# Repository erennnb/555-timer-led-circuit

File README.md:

# ⚡ NE555 Timer — Blinking LED Circuit

\<p align="center">
&#x20; \<strong>A simple circuit. A fundamental concept. A step into electronics.\</strong>
\</p>

\<p align="center">
&#x20; Designed with ❤️ and \<strong>KiCad\</strong>
\</p>

---

## 🔎 About The Project

This project is a blinking LED circuit built around the **NE555 timer IC**, one of the most widely used integrated circuits in electronics.

The goal is to explore the fundamentals of timing circuits, understand how electronic components work together, and take the first steps toward PCB design.

What starts as a single blinking LED becomes an opportunity to learn circuit design, component selection, schematic capture, and PCB layout.

## 🎯 Project Goals

- Understand the fundamentals of the NE555 timer.
- Explore timing circuits and oscillation.
- Practice schematic design in KiCad.
- Learn component placement and PCB routing.
- Build a foundation for more advanced electronics projects.

## 🧩 Components

| Component      | Purpose                                          |
| -------------- | ------------------------------------------------ |
| NE555 timer IC | Generates timing pulses                          |
| Resistors      | Set timing characteristics and limit LED current |
| Capacitor(s)   | Determine timing behavior                        |
| LED            | Visual output indicator                          |
| Power supply   | Provides circuit power                           |

*Component values and the exact configuration are documented in the KiCad project files.*

## 🛠️ Tools & Technologies

\<p>
&#x20; \
&#x20; \
\</p>

- **EDA Software:** KiCad
- **Main IC:** NE555
- **Design:** Electronic schematic and PCB layout

## 📂 Project Structure

```text
555-timer-led-circuit/
├── README.md
├── 555-timer-led-circuit.kicad_pro
├── 555-timer-led-circuit.kicad_sch
└── 555-timer-led-circuit.kicad_pcb
```

*Filenames may differ depending on the actual project files.*

## ✅ Project Status

- [x] Schematic design
- [x] PCB layout
- [x] Design Rule Check (DRC)
- [ ] Hardware testing

## 🚀 What I Learned

- Translating a circuit idea into a schematic.
- Understanding the role of the NE555 timer.
- Organizing electronic components in a PCB design.
- Developing a structured electronics design workflow.

## 🔮 Future Improvements

- Calculate and measure the LED blinking frequency.
- Compare theoretical timing with measured results.
- Refine PCB component placement and routing.
- Explore additional NE555 operating modes.

## 👨‍💻 About Me

I am an Electrical and Electronics Engineering student building practical skills in electronics, PCB design, and embedded systems.

This project is part of my journey from learning circuit fundamentals to designing more advanced electronic systems.

**One circuit at a time. One concept at a time.**

---

\<p align="center">
&#x20; \<i>Learning by designing, improving by building.\</i>
\</p>

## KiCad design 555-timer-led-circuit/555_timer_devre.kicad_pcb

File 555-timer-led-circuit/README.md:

# ⚡ NE555 Timer — Blinking LED Circuit

<p align="center">
  <strong>One IC. One LED. Endless possibilities to learn.</strong>
</p>

---

## 🔍 About The Project

This project is a **blinking LED circuit based on the NE555 timer IC**, designed using KiCad.

The NE555 operates as an astable multivibrator, continuously generating pulses that turn the LED on and off at regular intervals.

The purpose of this project is to gain practical experience in electronic circuit design, schematic development, PCB layout, and hardware design fundamentals.

## 📸 Project Gallery

### Circuit Schematic

### PCB Layout

### 3D PCB Visualization

---

## 🧩 Components

| Component | Function |
|---|---|
| NE555 Timer IC | Generates periodic pulses |
| Resistors | Control timing and LED current |
| Capacitor | Determines timing characteristics |
| LED | Visual output indicator |
| Power Supply | Provides operating voltage |

## ⚙️ How It Works

The NE555 is configured in astable mode.

1. The capacitor charges through the resistor network.
2. When the capacitor voltage reaches the upper threshold, the output changes state.
3. The capacitor discharges through the discharge path.
4. When the voltage reaches the lower threshold, the output changes again.
5. This cycle repeats continuously, causing the LED to blink.

The blinking frequency depends on the resistor and capacitor values.

## 🛠️ Design Tools

- **KiCad** — Schematic capture and PCB design
- **Gerber** — PCB manufacturing file format

## 📂 Repository Structure

```text
555-timer-led-circuit/
│
├── README.md
├── images/
│   ├── schematic.png
│   ├── pcb-layout.png
│   └── 3d-view.png
│
├── gerber/
│
├── 555_timer_devre.kicad_pro
├── 555_timer_devre.kicad_sch
└── 555_timer_devre.kicad_pcb
```

## ✅ Project Progress

- [x] Circuit schematic design
- [x] Component selection
- [x] PCB layout
- [x] Gerber file preparation
- [ ] Physical PCB production
- [ ] Hardware testing

## 📚 What I Learned

- Understanding the NE555 timer IC.
- Learning the astable multivibrator configuration.
- Creating electronic schematics with KiCad.
- Component placement and PCB routing.
- Preparing PCB manufacturing files.

## 🚀 Future Improvements

- Measure the actual LED blinking frequency.
- Compare theoretical and measured timing values.
- Improve PCB layout and component placement.
- Experiment with different resistor and capacitor values.
- Build more advanced timer-based circuits.

---

## 👨‍💻 About Me

I am an Electrical and Electronics Engineering student interested in electronics, PCB design, embedded systems, and hardware development.

This repository is part of my practical learning journey, where I document my projects, experiments, and progress in electronics engineering.

<p align="center">
  <strong>Learn. Design. Build. Repeat.</strong>
</p>

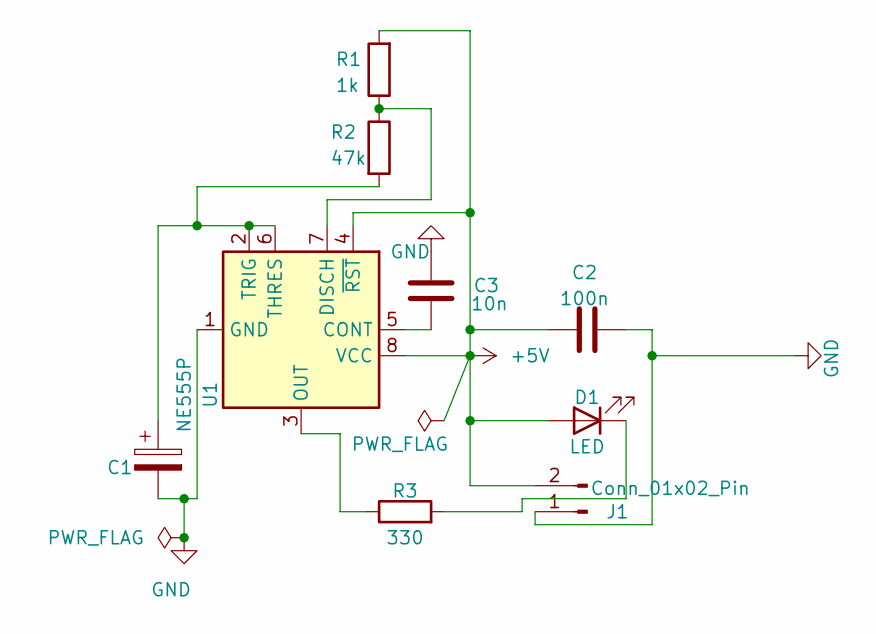
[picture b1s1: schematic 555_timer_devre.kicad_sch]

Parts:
C1: 10u; CP_Radial_D5.0mm_P2.00mm
C2: 100n; C_Disc_D5.0mm_W2.5mm_P5.00mm
C3: 10n; C_Disc_D5.0mm_W2.5mm_P5.00mm
D1: LED; LED_D5.0mm
J1: Conn_01x02_Pin; PinHeader_1x02_P2.54mm_Vertical
R1: 1k; R_Axial_DIN0207_L6.3mm_D2.5mm_P10.16mm_Horizontal
R2: 47k; R_Axial_DIN0207_L6.3mm_D2.5mm_P10.16mm_Horizontal
R3: 330; R_Axial_DIN0207_L6.3mm_D2.5mm_P10.16mm_Horizontal
U1: NE555P; DIP-8_W7.62mm

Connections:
+5V: C2.2, D1.2 (A), J1.2, R1.2, U1.4 (~RST), U1.8 (VCC)
GND: C1.2, C2.1, C3.1, J1.1, U1.1 (GND)
unnamed: D1.1 (K), R3.2
unnamed: C3.2, U1.5 (CONT)
unnamed: R1.1, R2.1, U1.7 (DISCH)
unnamed: R3.1, U1.3 (OUT)
unnamed: C1.1, R2.2, U1.2 (TRIG), U1.6 (THRES)

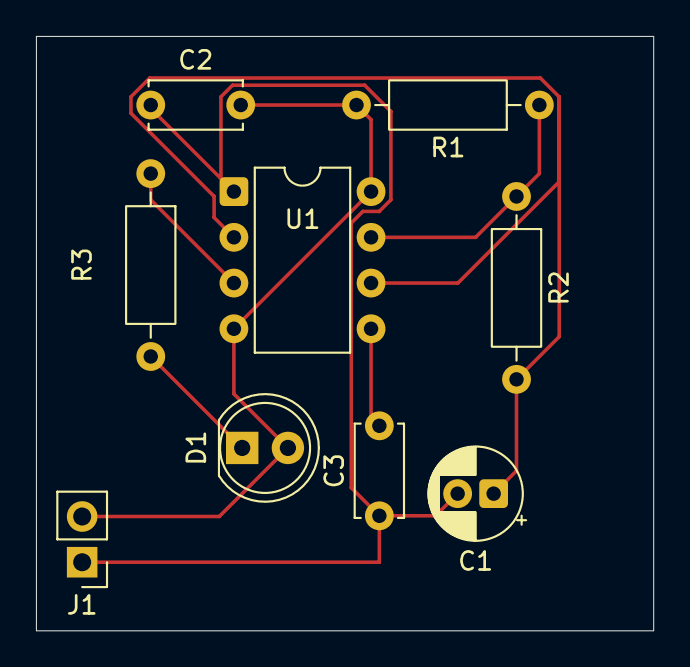
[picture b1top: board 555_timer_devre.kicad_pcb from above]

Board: 2 copper layers, 34.3 x 33.0 mm, 9 parts (0 on the bottom side), 7 nets.
